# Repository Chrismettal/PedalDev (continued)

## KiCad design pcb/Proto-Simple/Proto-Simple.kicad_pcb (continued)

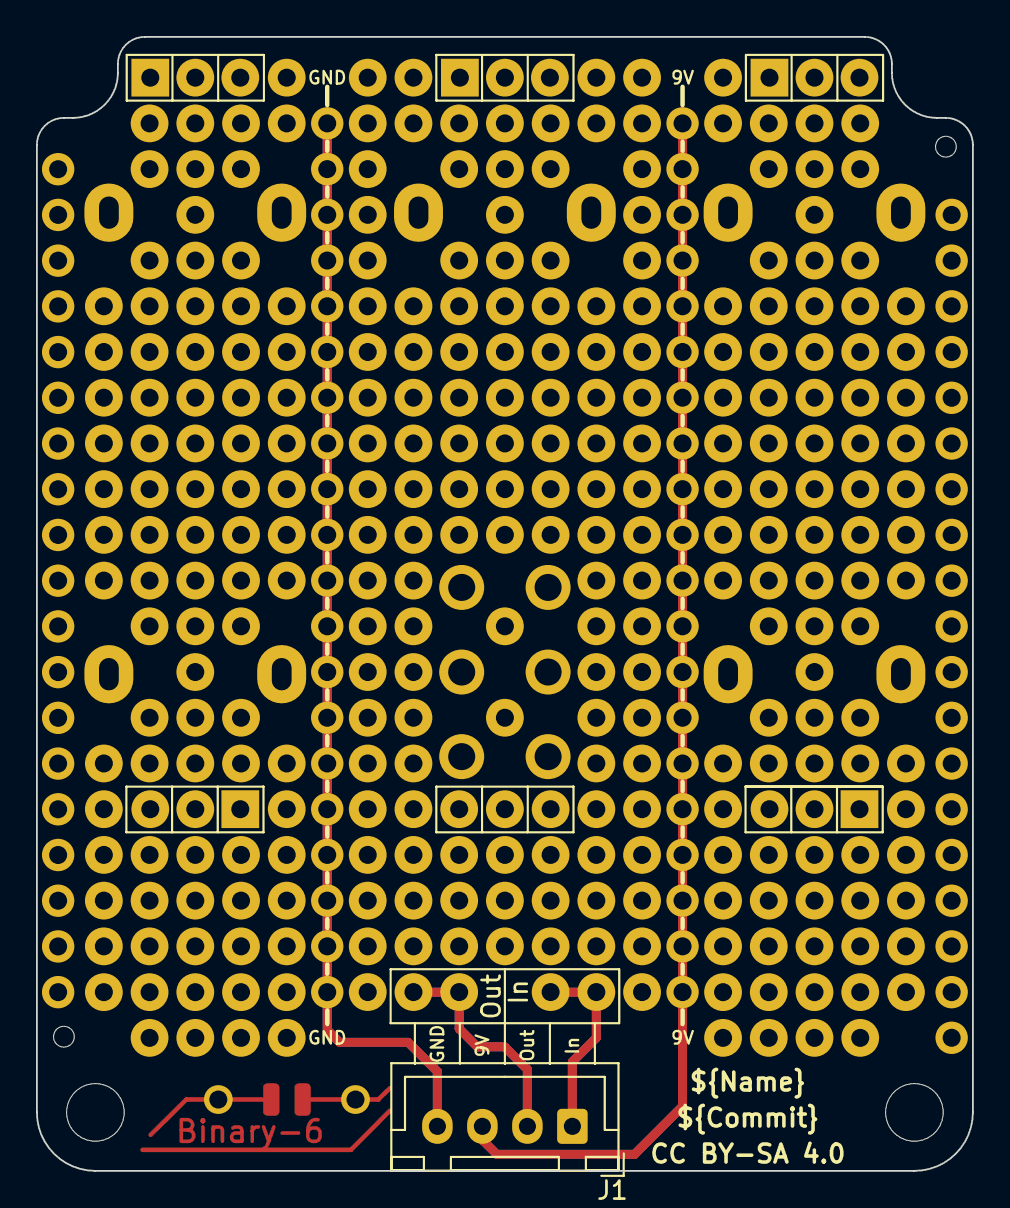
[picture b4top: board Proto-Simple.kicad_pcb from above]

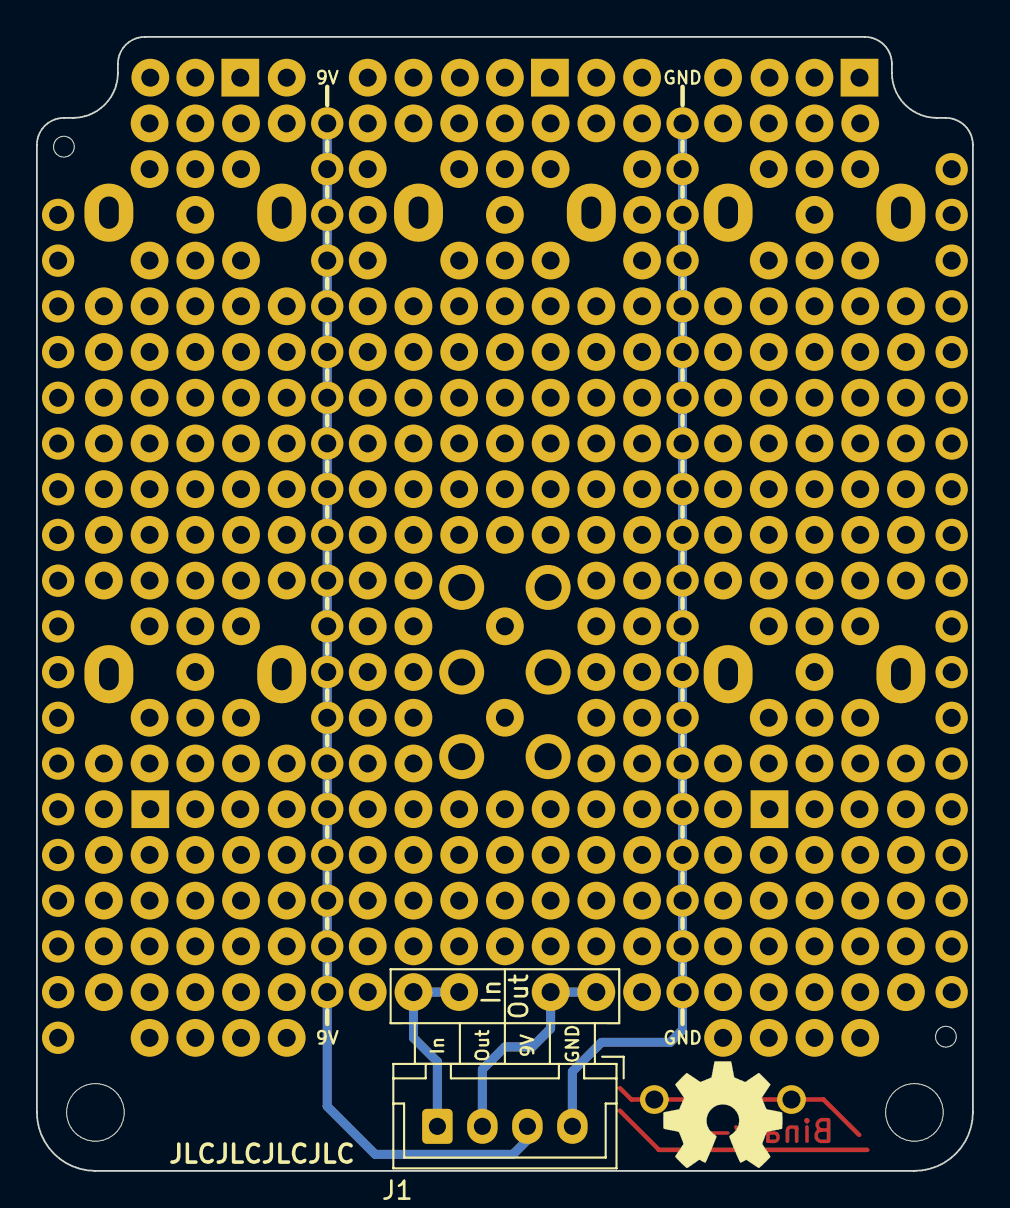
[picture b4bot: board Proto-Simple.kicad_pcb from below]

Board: 2 copper layers, 52.0 x 63.0 mm, 53 parts (5 on the bottom side), 4 nets.

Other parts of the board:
H7: Symbol_Binary6; Binary_6_v0.1_tiny_silk
MK2, MK2#2: Mounting_Hole_M3; EigenesMountingHole_3.2mm_M3_Small
RV100, RV101, RV102, RV200, RV200#2: 100K Lin; Potentiometer_Alpha_RD901F-40-00D_Single_Vertical

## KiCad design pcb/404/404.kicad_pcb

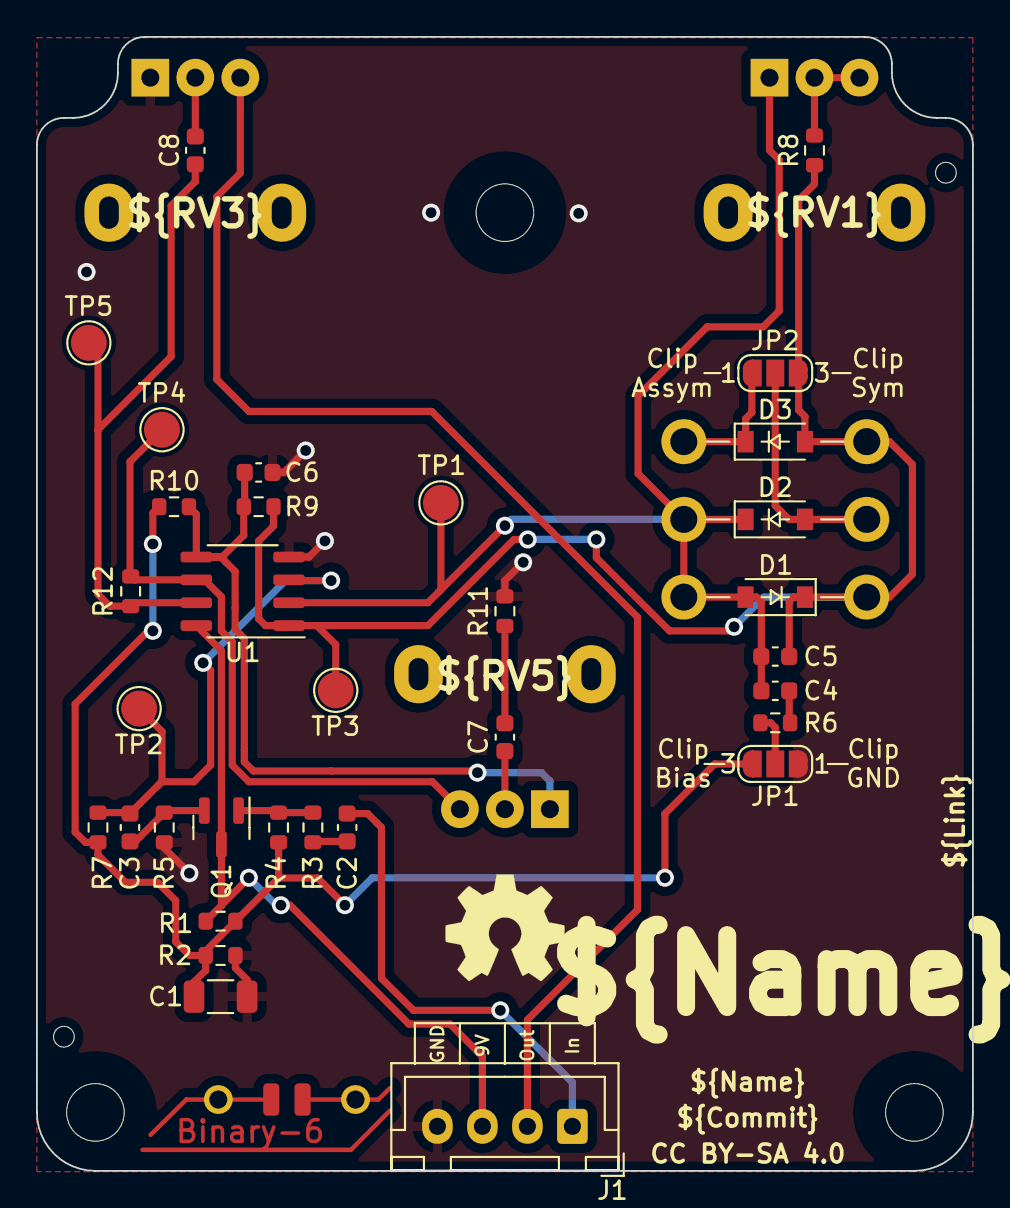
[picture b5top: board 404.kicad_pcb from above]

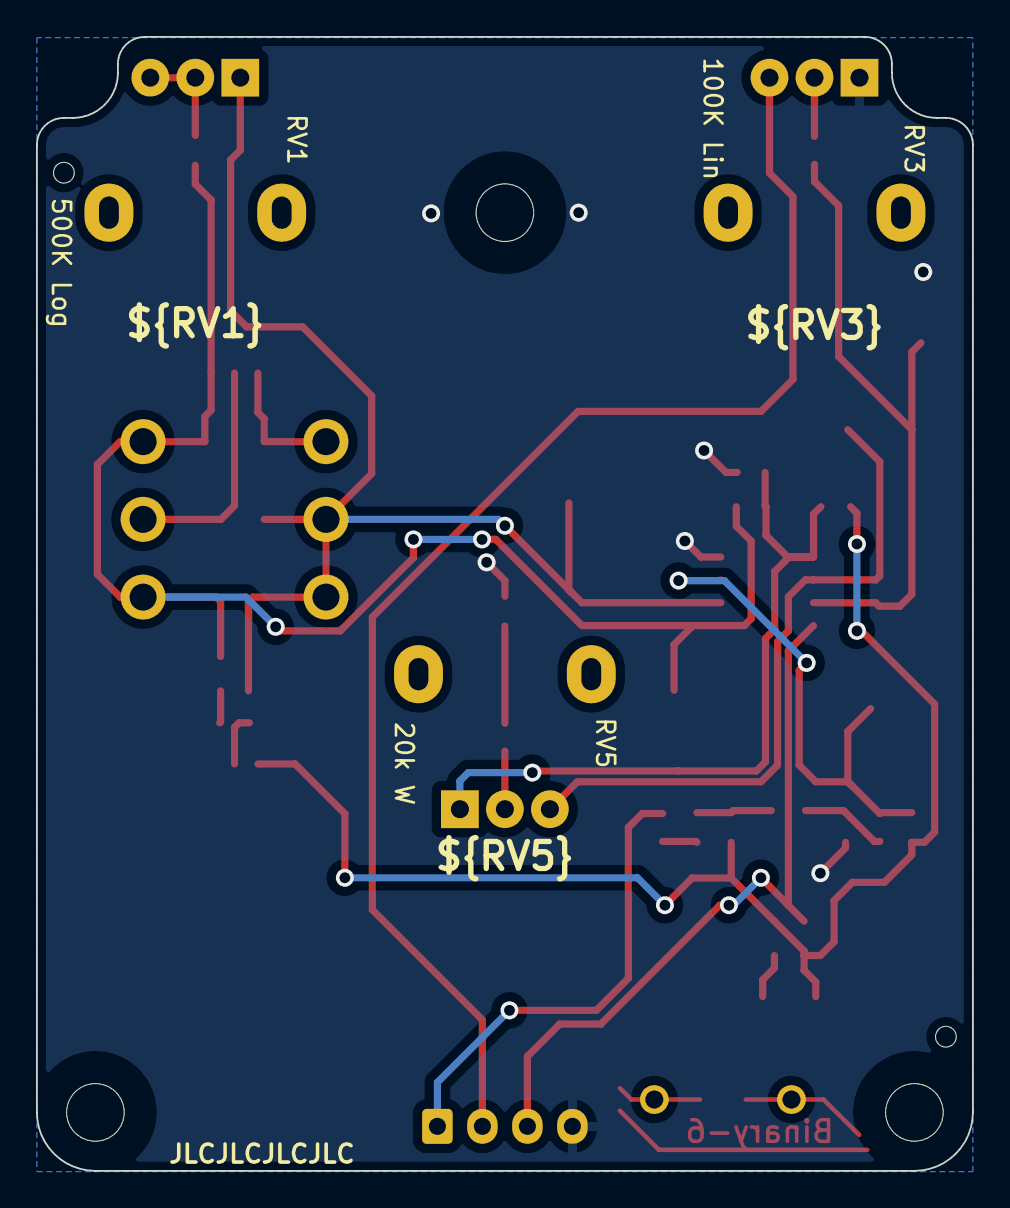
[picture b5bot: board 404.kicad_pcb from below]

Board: 2 copper layers, 52.0 x 63.0 mm, 40 parts (3 on the bottom side), 22 nets.

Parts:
C1: 22uF; C_1206_3216Metric
C2, C4: 47n; C_0603_1608Metric
C3, C8: 1uF; C_0603_1608Metric
C5: 47pF; C_0603_1608Metric
C6, C7: 220nF; C_0603_1608Metric
D1, D2, D3: 1N4148W; D_SOD-123+THT
H7: Symbol_Binary6; Binary_6_v0.1_tiny_silk
J1: Conn_01x04; JST_XH_B4B-XH-A_1x04_P2.50mm_Vertical
JP1, JP2: SolderJumper; SolderJumper-3_P1.3mm_Open_RoundedPad1.0x1.5mm_NumberLabels
MK2, MK2#2, MK2#3: Mounting_Hole_M3; EigenesMountingHole_3.2mm_M3_Small
Q1: BC846; SOT-23
R1, R2, R5, R7, R10: 10K; R_0603_1608Metric
R3, R9, R12: 1K; R_0603_1608Metric
R4: 510K; R_0603_1608Metric
R6: 4K7; R_0603_1608Metric
R8: 51K; R_0603_1608Metric
R11: 220R; R_0603_1608Metric
RV1: 500K Log; Potentiometer_Alpha_RD901F-40-00D_Single_Vertical
RV3: 100K Lin; Potentiometer_Alpha_RD901F-40-00D_Single_Vertical
RV5: 20k W; Potentiometer_Alpha_RD901F-40-00D_Single_Vertical
TP1, TP2, TP3, TP4, TP5: TP; TestPoint_Pad_D2.0mm
U1: RC4558; SO-8_3.9x4.9mm_P1.27mm

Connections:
+4V5: C1.1, JP1.3 (B), R1.2, R2.1, R4.1, R7.1, R10.1
+9V: J1.3, Q1.3 (C), R1.1, U1.8 (V+)
GND: C1.2, C6.2, J1.4, JP1.1 (A), R2.2, R5.2, R11.2, RV3.1, U1.4 (V-)
unnamed: C2.2, R3.1
unnamed: C3.1, Q1.2 (E), R5.1
unnamed: C3.2, R7.2, TP2.1, U1.3 (+)
unnamed: C4.1, C5.1, D1.2 (A), D2.1 (K), RV1.1, TP1.1, U1.2 (-)
unnamed: C4.2, R6.2
unnamed: C5.2, D1.1 (K), D3.2 (A), JP2.3 (B), R8.1, R9.1, TP3.1, U1.1
unnamed: C6.1, R9.2, R10.2, RV5.1, U1.5 (+)
unnamed: C7.1, RV5.2
unnamed: C7.2, R11.1
unnamed: C8.1, R12.2, TP5.1, U1.7
unnamed: C8.2, RV3.2
unnamed: D2.2 (A), JP2.2 (C)
unnamed: D3.1 (K), JP2.1 (A)
unnamed: JP1.2 (C), R6.1
unnamed: Q1.1 (B), R3.2, R4.2
unnamed: R8.2, RV1.2, RV1.3
unnamed: R12.1, RV5.3, TP4.1, U1.6 (-)
Upper_PCB_Input: C2.1, J1.1
Upper_PCB_Output: J1.2, RV3.3

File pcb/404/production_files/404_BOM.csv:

Comment,Designator,Footprint,LCSC
"22uF","C1","Capacitor_SMD:C_1206_3216Metric","C12891"
"47n","C2,C4","Capacitor_SMD:C_0603_1608Metric","C1622"
"1uF","C3,C8","Capacitor_SMD:C_0603_1608Metric","C15849"
"47pF","C5","Capacitor_SMD:C_0603_1608Metric","C1671"
"220nF","C6,C7","Capacitor_SMD:C_0603_1608Metric","C21120"
"1N4148W","D1,D2,D3","MeineBib:D_SOD-123+THT","C81598"
"Conn_01x04","J1","Connector_JST:JST_XH_B4B-XH-A_1x04_P2.50mm_Vertical","C144395"
"BC846","Q1","Package_TO_SOT_SMD:SOT-23","C87062"
"10K","R1,R2,R5,R7,R10","Resistor_SMD:R_0603_1608Metric","C25804"
"220R","R11","Resistor_SMD:R_0603_1608Metric","C22962"
"1K","R3,R9,R12","Resistor_SMD:R_0603_1608Metric","C21190"
"510K","R4","Resistor_SMD:R_0603_1608Metric","C23192"
"4K7","R6","Resistor_SMD:R_0603_1608Metric","C23162"
"51K","R8","Resistor_SMD:R_0603_1608Metric","C23196"
"500K","RV1","Potentiometer_THT:Potentiometer_Alpha_RD901F-40-00D_Single_Vertical",""
"20k","RV2","Potentiometer_THT:Potentiometer_Alpha_RD901F-40-00D_Single_Vertical",""
"100K","RV3","Potentiometer_THT:Potentiometer_Alpha_RD901F-40-00D_Single_Vertical",""
"RC4558","U1","Package_SO:SO-8_3.9x4.9mm_P1.27mm","C406864"

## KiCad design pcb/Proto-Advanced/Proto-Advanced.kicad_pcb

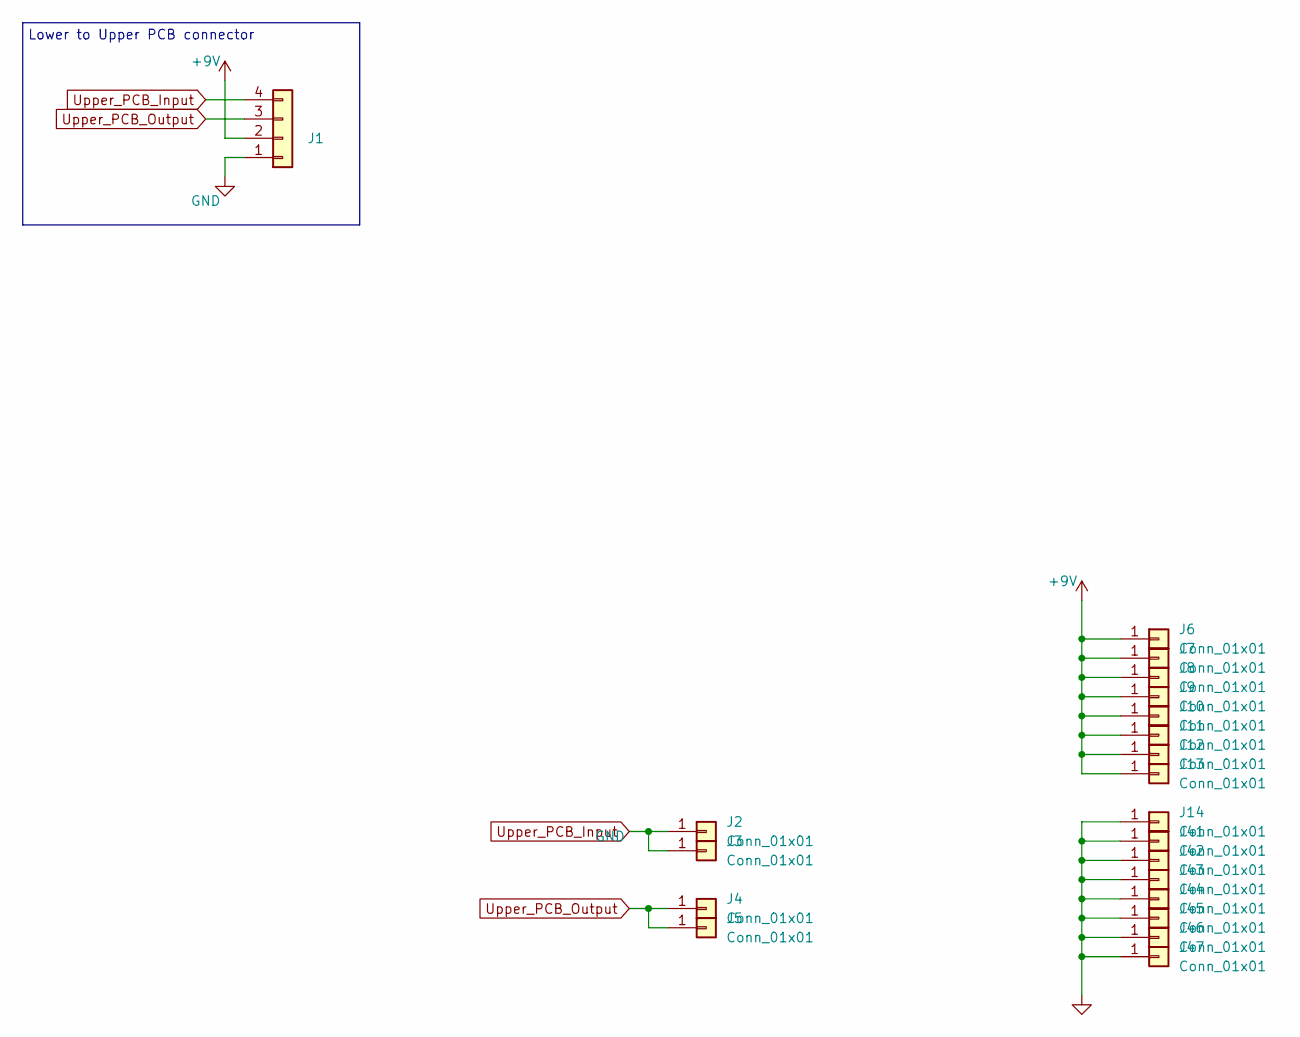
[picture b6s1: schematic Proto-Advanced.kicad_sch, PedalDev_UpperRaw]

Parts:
J1: LCSC C144395
J2, J3, J4, J5, J6, J7, J8, J9, J10, J11, J12, J13, J14, J41, J42, J43, J44, J45, J46, J47: Conn_01x01; Protopin

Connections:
+9V: J1.2, J6.1, J7.1, J8.1, J9.1, J10.1, J11.1, J12.1, J13.1
GND: J1.1, J14.1, J41.1, J42.1, J43.1, J44.1, J45.1, J46.1, J47.1
Upper_PCB_Input: J1.4, J2.1, J3.1
Upper_PCB_Output: J1.3, J4.1, J5.1

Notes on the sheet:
Lower to Upper PCB connector

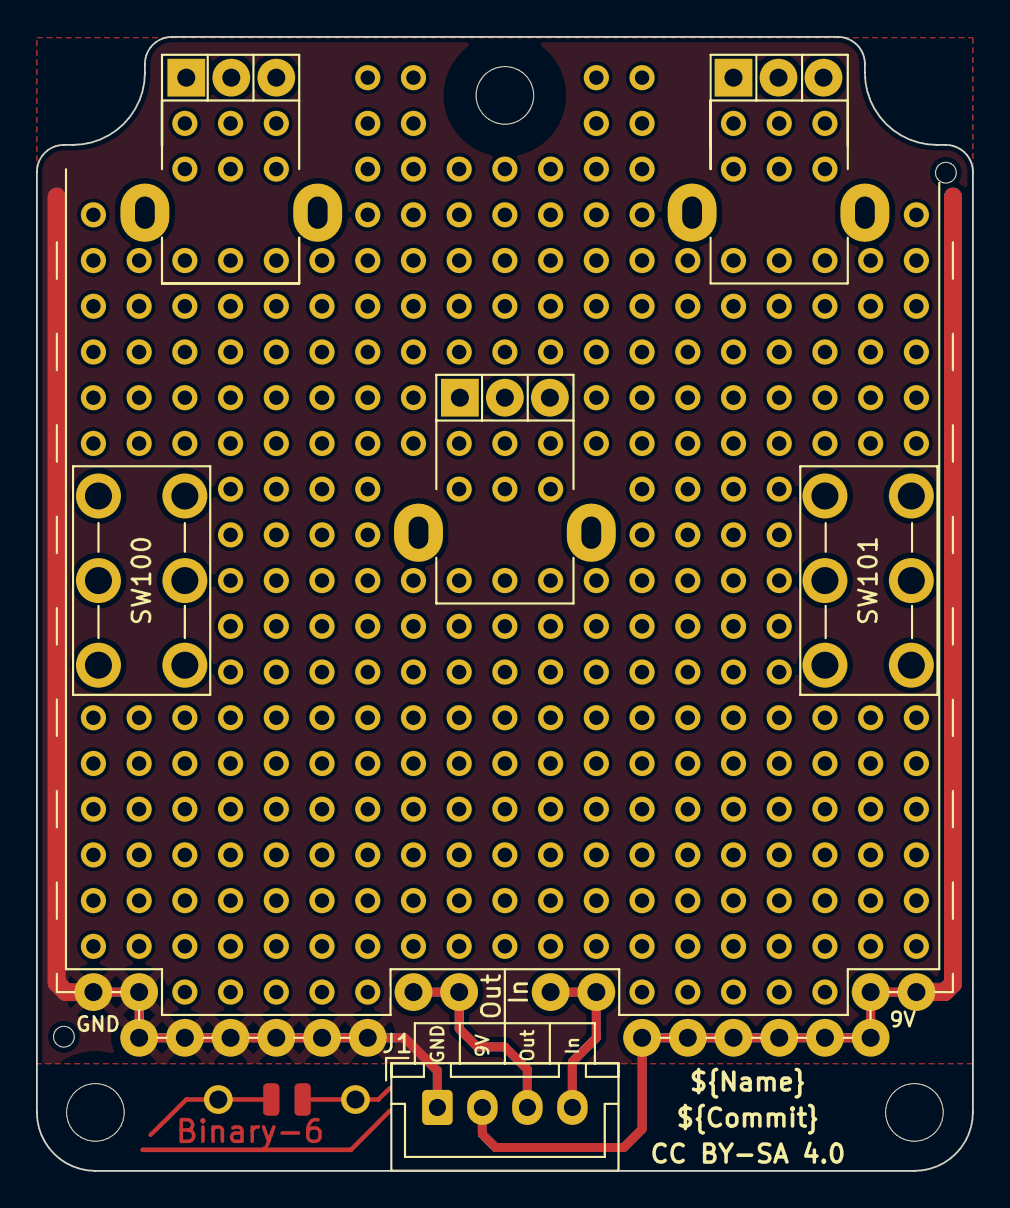
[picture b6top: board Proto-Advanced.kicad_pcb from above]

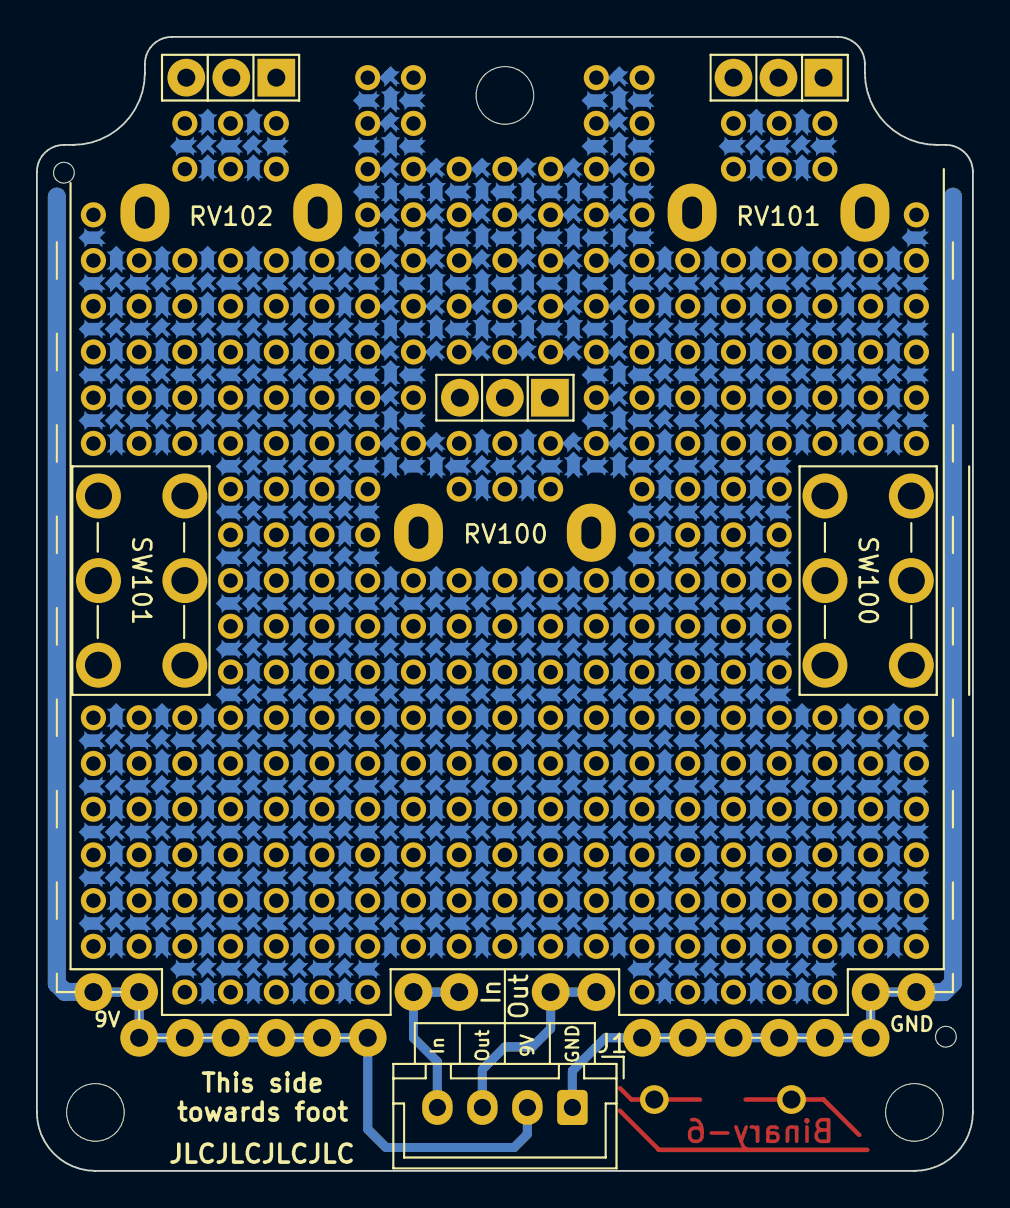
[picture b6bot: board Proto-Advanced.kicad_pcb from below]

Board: 2 copper layers, 52.0 x 63.0 mm, 30 parts (5 on the bottom side), 4 nets.

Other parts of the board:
H7: Symbol_Binary6; Binary_6_v0.1_tiny_silk
MK2, MK2#2, MK2#3: Mounting_Hole_M3; EigenesMountingHole_3.2mm_M3_Small
RV100, RV101, RV102: 100K Lin; Potentiometer_Alpha_RD901F-40-00D_Single_Vertical
SW100, SW101: SW_DPDT_x2; Switch_toggle_DPDT_Print

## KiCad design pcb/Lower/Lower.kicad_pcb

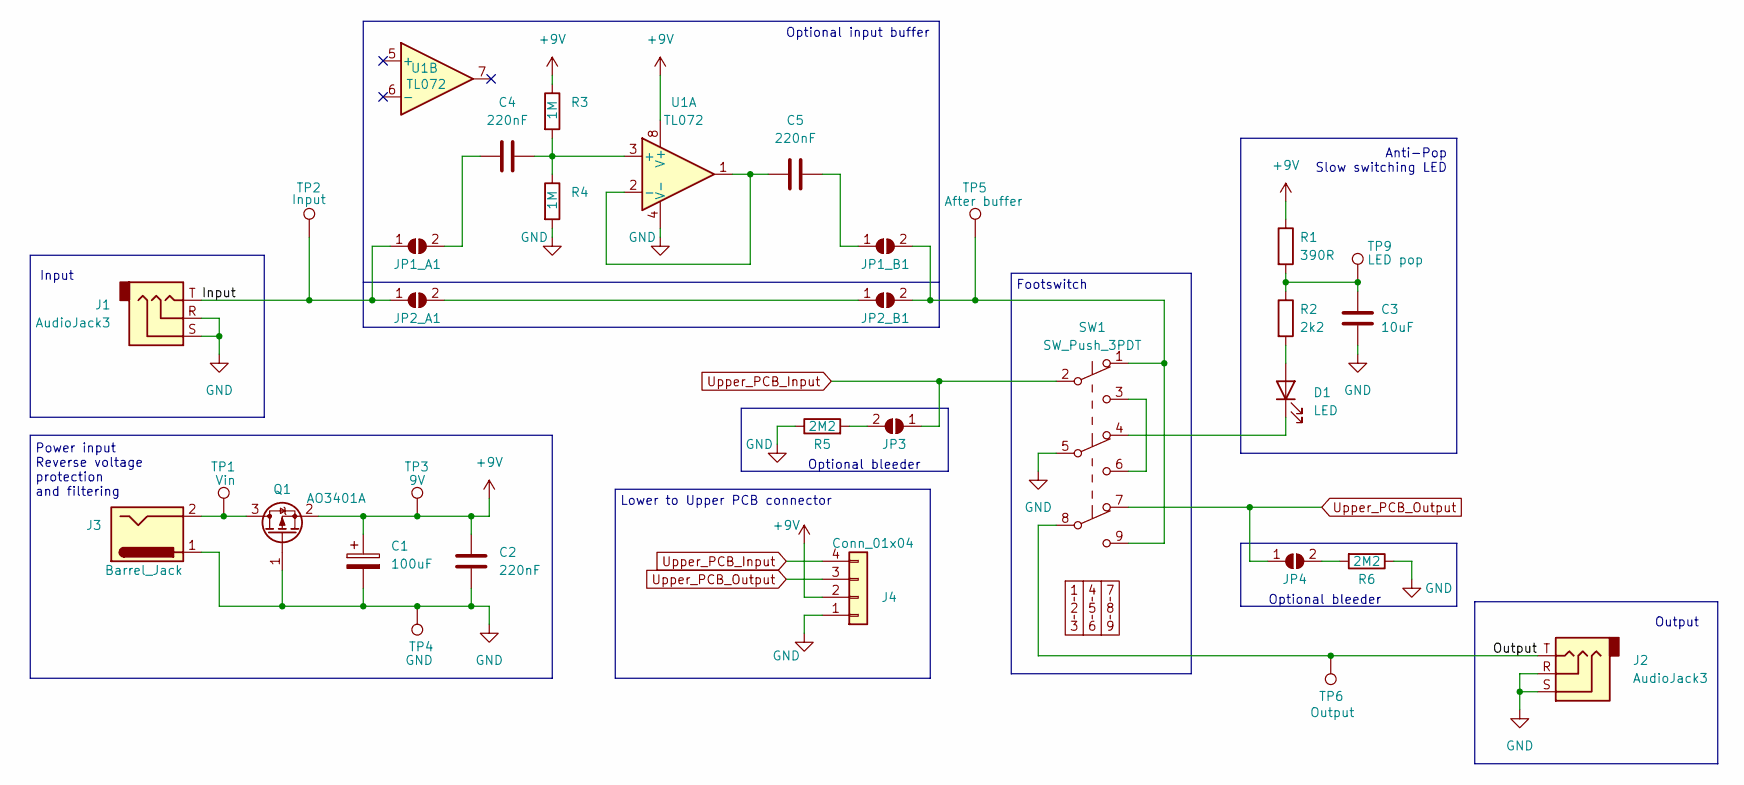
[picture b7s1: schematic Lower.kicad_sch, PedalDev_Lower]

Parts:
C1: 100uF; CP_Radial_D5.0mm_P2.00mm; LCSC C108360
C2, C4, C5: 220nF; C_0603_1608Metric; LCSC C21120
C3: 10uF; C_0805_2012Metric; LCSC C15850
D1: LED; LED_D5.0mm; LCSC C417347
J1, J2: AudioJack3; Audio_Jack_PJ-602B
J3: Barrel_Jack; DC_Barrel_Jack_Thinline_Wired_Standing
J4: Conn_01x04; PinSocket_1x04_P2.54mm_Vertical
JP1_A1, JP1_B1, JP2_A1, JP2_B1, JP3, JP4: Jmp; SolderJumper-2_P1.3mm_Open_TrianglePad1.0x1.5mm
Q1: AO3401A; SOT-23; LCSC C15127
R1: 390R; R_0603_1608Metric
R2: 2k2; R_0603_1608Metric
R3, R4: 1M; R_0603_1608Metric
R5, R6: 2M2; R_0603_1608Metric
SW1: SW_Push_3PDT; Footswitch_3PDT
TP1: Vin; TestPoint_Pad_D2.0mm
TP2: Input; TestPoint_Bridge_Pitch2.54mm_Drill1.0mm
TP3: 9V; TestPoint_Pad_D2.0mm
TP4: GND; TestPoint_Bridge_Pitch2.54mm_Drill1.0mm
TP5: After buffer; TestPoint_Pad_D2.0mm
TP6: Output; TestPoint_Bridge_Pitch2.54mm_Drill1.0mm
TP9: LED pop; TestPoint_Pad_D2.0mm
U1: TL072; SOIC-8_3.9x4.9mm_P1.27mm; LCSC C6961

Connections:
+9V: C1.1, C2.1, J4.2, Q1.2 (S), R1.1, R3.1, TP3.1, U1.8 (V+)
/Input: J1.T, JP1_A1.1 (A), JP2_A1.1 (A), TP2.1
/Output: J2.T, SW1.8 (B), TP6.1
GND: C1.2, C2.2, C3.2, J1.R, J1.S, J2.R, J2.S, J3.1, J4.1, Q1.1 (G), R4.2, R5.1, R6.1, SW1.5 (B), TP4.1, U1.4 (V-)
unnamed: C3.1, R1.2, R2.1, TP9.1
unnamed: C4.1, JP1_A1.2 (B)
unnamed: C4.2, R3.2, R4.1, U1.3 (+)
unnamed: C5.1, U1.1, U1.2 (-)
unnamed: C5.2, JP1_B1.1 (A)
unnamed: D1.1 (K), SW1.4 (A)
unnamed: D1.2 (A), R2.2
unnamed: J3.2, Q1.3 (D), TP1.1
unnamed: JP1_B1.2 (B), JP2_B1.2 (B), SW1.1 (A), SW1.9 (C), TP5.1
unnamed: JP2_A1.2 (B), JP2_B1.1 (A)
unnamed: JP3.2 (B), R5.2
unnamed: JP4.2 (B), R6.2
unnamed: SW1.3 (C), SW1.6 (C)
Upper_PCB_Input: J4.4, JP3.1 (A), SW1.2 (B)
Upper_PCB_Output: J4.3, JP4.1 (A), SW1.7 (A)

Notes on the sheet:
Optional input buffer
Input
Footswitch
Power input Reverse voltage protection and filtering
Output
Optional bleeder
Lower to Upper PCB connector
Anti-Pop Slow switching LED

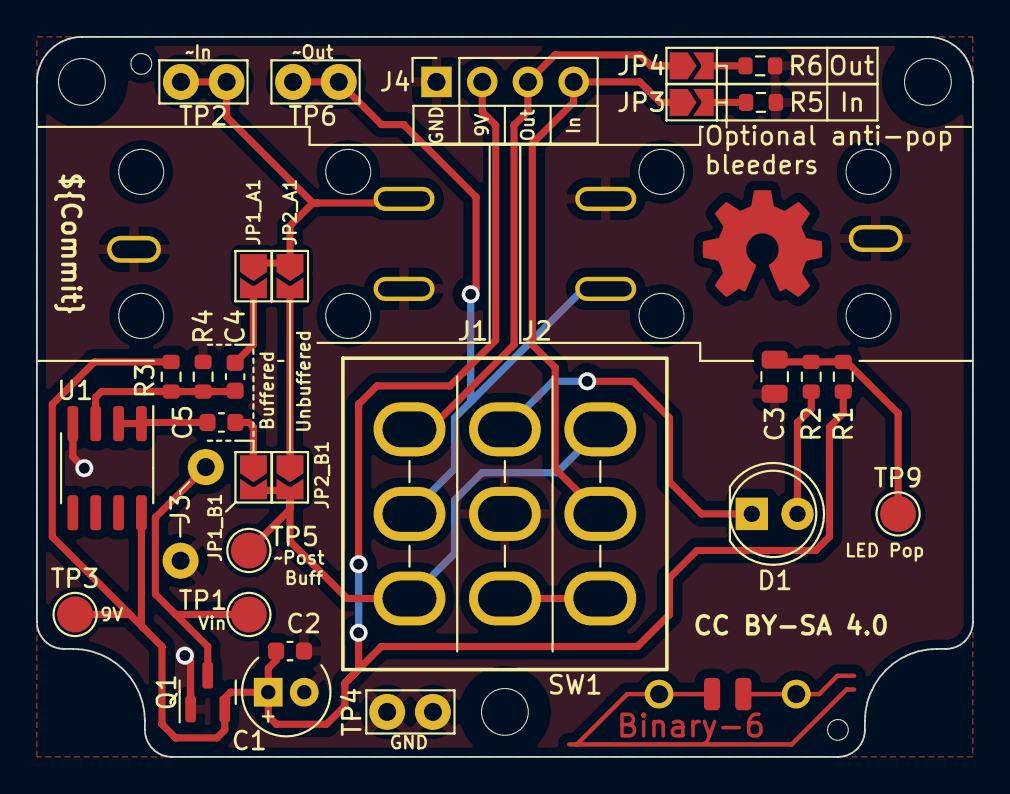
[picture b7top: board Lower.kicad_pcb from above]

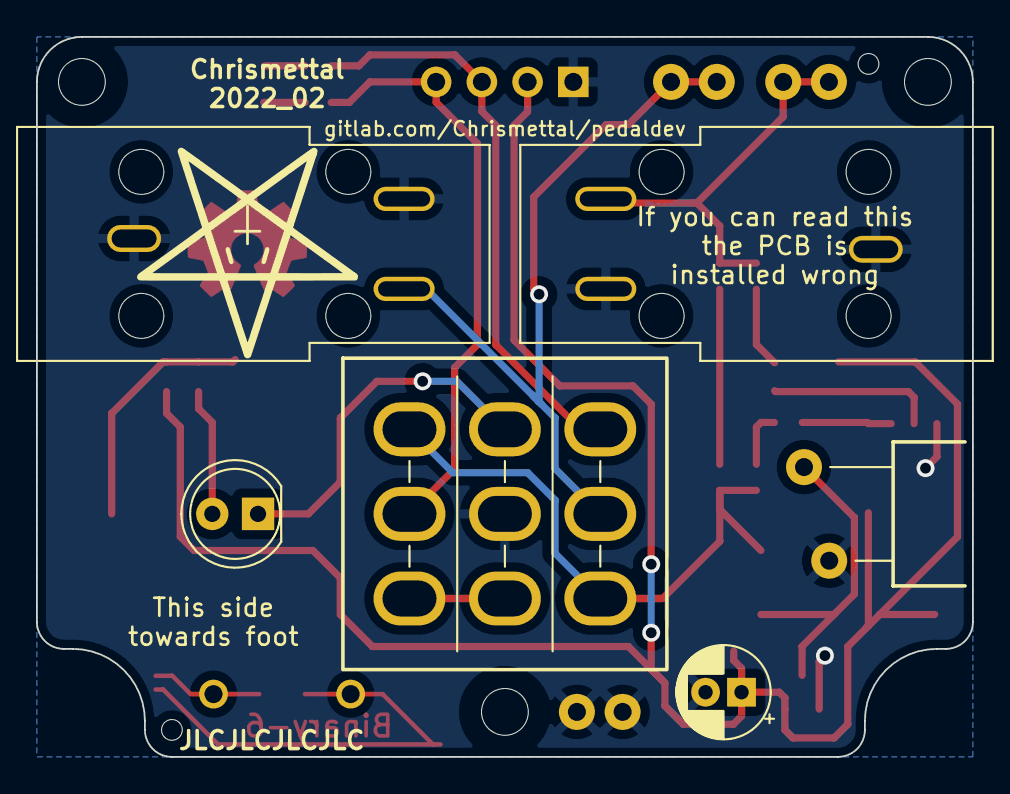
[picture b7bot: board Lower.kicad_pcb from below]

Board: 2 copper layers, 52.0 x 40.0 mm, 37 parts (7 on the bottom side), 19 nets.

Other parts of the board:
H7: Symbol_Binary6; Binary_6_v0.1_tiny_silk
MK2, MK2#2, MK2#3: Mounting_Hole; EigenesMountingHole_2.6mm_M2.5_Small
MK6: PentThin

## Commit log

2022-02-17 Initial template commit
2022-02-17 Create lower PCB schematic
2022-02-17 Assign Lower PCB footprints and BOM codes
2022-02-18 [Lower] Start adding devices to PCB
2022-02-18 [Lower] Design and add more footprints
2022-02-18 [Lower] Start mechanical design
2022-02-18 Add sources to Readme
2022-02-18 [Lower] Continue mechanical design
2022-02-18 [Lower] Fix some footprints 3D models
2022-02-18 [Lower] Add DRC rules and set board stackup parameters
2022-02-18 [Lower] Remove 3D object from connector footprint
2022-02-18 [Lower] Move mechanical parts to fit enclosure
2022-02-19 [Lower] Update Anti-Pop circuit after testing
2022-02-19 [Lower] Fix board outline and update 3D components to scaled VRMLs
2022-02-19 Remove dummy file
2022-02-19 [Lower] Pinswap PCB-PCB connector
2022-02-20 [Lower] Move 3PDT 3D thingy
2022-02-20 [Lower] Make PCB smaller
2022-02-20 [Lower] Swap out C1 footprint / LCSC part for THT one
2022-02-20 [Lower] Fix LED wiring in Schematic, route whole board
2022-02-20 [Lower] Pour ground
2022-02-20 [Lower] Push some parts around a bit
2022-02-20 [Lower] Fix DRC violations
2022-02-20 Add BaseRaw FreeCAD project, including Lower PCB but only simulation of upper one
2022-02-20 [BaseRaw] Add mechanical parts for simulation of maximal configuration
2022-02-20 [BaseRaw] Push mechanical parts around until i'm happy
2022-02-21 [UpperRaw] Create raw upper PCB as a base for creating individual models
2022-02-22 [UpperRaw] swap mounting holes for M3 ones
2022-02-23 [Lower] Beautify silk and add logos
2022-02-24 [Lower] Beautify silk - should be ready to order
2022-02-24 [Lower] Update commit hash
2022-02-24 [Lower] Update gerber output preferences
2022-02-24 [Lower] Minor update to schematic BOM before ordering
2022-02-25 [Lower] Add tooling holes and repo link
2022-02-25 [UpperRaw] Create template with logos, tooling holes etc.
2022-02-25 [UppwerRaw] Update mechanically a bit before importing into case
2022-02-25 [BaseRaw] Import UpperRaw and Lower PCBs into case
2022-02-27 [Lower] Add measurements
2022-02-27 [BaseRaw] Add holes according to actual upper PCB
2022-02-27 [ProtoSimple] Add simple protoboard first version
2022-02-27 [ProtoSimple] update Schematic
2022-02-27 [ProtoAdvanced] Add advanced protoboard first version
2022-02-27 [Screamer] Start adding Screamer-style schematic
2022-03-02 [Screamer] update schematic and assign LCSC parts
2022-03-04 [Screamer] Update PCB with schematic updates
2022-03-05 [Screamer] Update diode footprint and start arranging stuff on PCB
2022-03-05 Add #auto_saved_files# to .gitignore
2022-03-05 [Screamer] Initially route Screamer PCB
2022-03-05 [404] Update PCB
2022-03-05 [UpperRaw] Add symbols from 404 PCB
2022-03-05 [LowerBuffer] Start creating buffered lower schematic
2022-03-05 [LowerBuffer] Fiddle with Schematic, looking for flip flop solutions
2022-03-19 [ProtoSimple] Generate gerber files
2022-03-19 [ProtoAdvanced] Fix some Silk lines
2022-03-19 [ProtoAdvanced] Generate gerber files
2022-04-17 Add new support link to readme
2022-04-18 Update readme with shields
2022-04-24 [ProtoAdvanced] Update proto footprints with new tolerances
2022-04-24 [ProtoSimple] Update proto footprints for bigger pads
2022-04-24 [ProtoAdvanced][ProtoSimple] Make power rails wider
2022-04-24 [All] Update all pot footprints and silkscreens
2022-04-24 [Lower] Add standoff STEP to LED
2022-04-24 [404] Rename board; Update silk jumper description
2022-04-24 [All] Add LCSC part number for JST connector
2022-04-24 [404] Export gerbers/pos/bom
2022-04-24 Add production files folder to repo
2022-04-24 Move production files into their pcb folders
2022-04-24 [All] Find out that the upper left pot is 0,08mm off on all designs
2022-04-24 [404] Recreate gerbers and pos file after last commits fix
2022-04-24 [Doc] Start adding headers to readme
2022-04-24 [FrontRaw] Start creating raw frontpanel
2022-04-24 [FrontRaw] Continue graphical design on frontpanel
2022-04-24 [FrontRaw] Add copper zones and keepout
2022-04-24 Add Frontpanel to 3D simu and update other boards. UpperRaw has pads still misaligned in simu
2022-04-25 [FrontRaw] Minor mask update around Binary logo and set grid origin
2022-04-25 [404] Create 404 frontpanel without any design yet
2022-04-25 [FrontRaw] Make controls font bigger
2022-04-25 [FrontRaw][404] Add a decorative bar as all I can think of for a "design"
2022-04-25 [404] Change my mind on the design. Wires it is.
2022-04-25 [404] Push some frontpanel stuff around
2022-04-25 [404] Minor frontpanel design update. Export gerbers
2022-04-25 [FrontRaw] Make title non italic
2022-04-25 [Doc] Add information to readme, preparing for a release
2022-04-26 [ProtoSimple] Generate gerbers
2022-04-29 [UpperRaw] Figure out new pot positions for 6 pots
2022-04-30 [AllRaw] Update base templates to 6 controls design
2022-04-30 [UpperRaw] Swap pot footprints
2022-04-30 [404] Recreate Upper and Front PCBs according to new base templates
2022-04-30 [404] Remove invalidated production files
2022-04-30 [404] Minor design improvements
2022-04-30 Update FreeCAD project with new 6 controls design
2022-05-01 [ProtoSimple] Recreate PCB according to new base template
2022-05-01 [ProtoAdvanced] Delete for now. Recreate later from simple version
2022-05-01 [404] Delete deprecated production files
2022-05-01 [TOP] Copy raw designs into new project
2022-05-01 [TOP] Start schematic while debating the layout
2022-05-04 [TOP] Draw schematic input and distortion stages
2022-05-07 [ProtoSimple] Remove production files
2022-05-07 [All] Flip board to board connector on upper PCB (obstructed some silk)
2022-05-07 [TOP] Continue schematic
2022-05-08 [TOP] Finish initial work on schematic
2022-05-08 [TOP] BOM consolidation
2022-05-08 [TOP] Assign footprints and LCSC part numbers
2022-05-08 [TOP] Consolidate footprints; Add bypass cap to U1
2022-05-08 [TOP] Route power, input and gain stages
2022-05-08 [TOP] Finish initial PCB design
2022-05-08 [TOP] Run and fix DRC
2022-05-08 [TOP] Optimize silkscreen designs
2022-05-08 [TOP] Optimize some tracks and pours
2022-05-08 [Doc] Add soldering requirements to README
2022-05-08 [TOP] Move some silkscreen designators
2022-05-08 [404][UpperRaw] Apply learned lessons from TOP:
    - Name on silk etc. is now a text variable
    - Optimized copypasta parts
    - Set pot footprint to my modified one
    - Rename pots ro always be RV1-6
    - Use text variables for pot names
    - Show pot values on silk
2022-05-08 [TOP] Forgot to save schematic after renaming testpoints
2022-05-09 [TOP] Create frontpanel
2022-05-15 [TOP] Move via to not overlap with silk
2022-05-15 Add dummy to production_files folders
2022-05-15 Checkpoint before exporting all of 404 and TOP
2022-05-15 [404] Fix frontpanel pent location
2022-05-15 [FrontRaw] Set gerber export settings
2022-05-15 [404] Export production files
2022-05-15 [ProtoSimple] Export production files
2022-05-15 [TOP] Export production files
2022-05-15 [All] Add 3D file for pointy pot knob to all upper boards
2022-05-15 [3D] Add existing PCBs to 3D project
2022-05-15 [LowerSmart] Add initial firmware
2022-05-15 [LowerSmart] Add eeprom read/write
2022-05-15 [LowerSmart] Add button debouncing and fix FET outputs
2022-05-16 [LowerSmart] Add some info to Readme and raise switching time
2022-05-20 [LowerSmart] Important refactor
2022-05-20 [LowerBuffer] Minor schematic cleanup
2022-05-20 [LowerSmart] Start schematic. Totally broken atm
2022-05-20 [LowerSmart] Minor refactor
2022-05-24 [LowerSmart] Fix source compile errors
2022-05-26 Minor formatting
2022-05-27 [3D] Add drill guide to 3d file
2022-05-27 [3D] Add top middle pot filler for <6 pot variants
2022-05-28 [3D] Update DrillGuide
2022-05-28 [Doc] Add building guide without pictures yet
2022-05-28 [3D] Lower drill tolerances on drill guide and make punch holes smaller
2022-05-28 [3D] Punch through drill guide numbers
2022-05-28 [Doc] Update readme drill guide
2022-05-28 [3D] Widen up drill guide punch holes a little bit
2022-05-29 [Doc] Add TOP debugging to readme
2022-05-29 [Doc] formatting
2022-05-29 [TOP] Remove broken production_files
2022-05-29 [TOP] Fix various problems of first design:
    - Some pins of TL072 swapped
    - Volume pot inverted
    - BOOST input of 7660 now only settable via jumper
    - Add option of TO-92/BF245 instead of SOT-23/BF545
    -
2022-05-29 [TOP] Schematic beautification
2022-06-05 [TOP] Fix 7660 -> 7660S in schematic; Make circuit fit for simulation of input stage
2022-06-05 idk tbh
2022-06-05 [Doc] Add debugging info to readme
2022-06-05 [Doc] Beautification
2022-06-05 [Doc] MORE beautification
2022-06-05 Revert "[3D] Widen up drill guide punch holes a little bit"
    This reverts commit 361226d20ffdb9c8150007e3a37046b2b2a5f396.
2022-06-05 [3D] Widen up most holes
2022-06-05 [3D] Add stp export for manufacturing
2022-06-07 [TOP] Update simulation parameters
2022-06-08 [Doc] Update readme while actually using build guide
2022-06-08 [3D] Fix pot mounting holes flipped the wrong way
2022-06-08 [3D] Export updated STEP file for manufacturing
2022-06-08 [3D] Update drill guide as well
2022-06-09 [Doc] Prepare readme for publishing
2022-06-09 Export 3d production files
2022-06-09 Export schematics for verified designs
2022-06-09 Try beautiful screenshots
2022-06-09 More pictures
2022-06-09 Even more beauty
2022-06-09 [Doc] Set all images to 50% width
2022-06-09 [DOc] Fix broken paragraph
2022-06-09 [Doc] Remove construction sign from ProtoSimple
2022-06-09 Add thumbnail
2022-06-09 [Doc] Add PJ-602B info to readme
2022-06-09 [Doc] Improve documentation
2022-06-12 [YW] Start reverse engineering
2022-06-12 [YW] Add to readme
2022-06-12 [YW] Add all devices to schematic and start wiring
2022-06-12 [YW] Continue reverse engineering
2022-06-13 [YW] Finish initial routing of schematic
2022-06-15 [YW] Schematic beautification before modifying
2022-06-15 [YW] Remove n. required stuff from schematic and modify to fit system
2022-06-15 [YW] Start creating PCB
2022-06-16 [YW] Finish initial version of PCB
2022-06-18 [YW] Rename project; Fix R6/R18 BOM
2022-06-18 [YW] Export production files
2022-06-18 [YW] Delete old project location
2022-06-18 [YW] Start creating front panel
2022-06-18 [YW] Finish initial frontpanel design
2022-06-18 [YW] Export frontpanel production files
2022-06-18 [TOP] Silk beautification
2022-06-18 [TOP] Export gerbers only for debugging
2022-07-05 [Doc] Add images for TOP and YOU WHAT
2022-07-07 [Doc] Update case and TOP information
2022-07-07 [Lower] Export production files
2022-09-27 [Lower] Fix LCSC part number for AO3401A (Was SOT-23-L3 instead of SOT-23)
2023-05-01 Remove Kofi; Remove Gitlab
